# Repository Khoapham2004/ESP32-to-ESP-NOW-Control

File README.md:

The second repository contains the hardware design of the robot. It is mostly based on the 2025 version, with updated sensors, the BTS signal removed from the previous design, and a PCB that primarily uses SMD components for improved compactness and reliability.

The following slide presents the control board developed for the 2026 project.

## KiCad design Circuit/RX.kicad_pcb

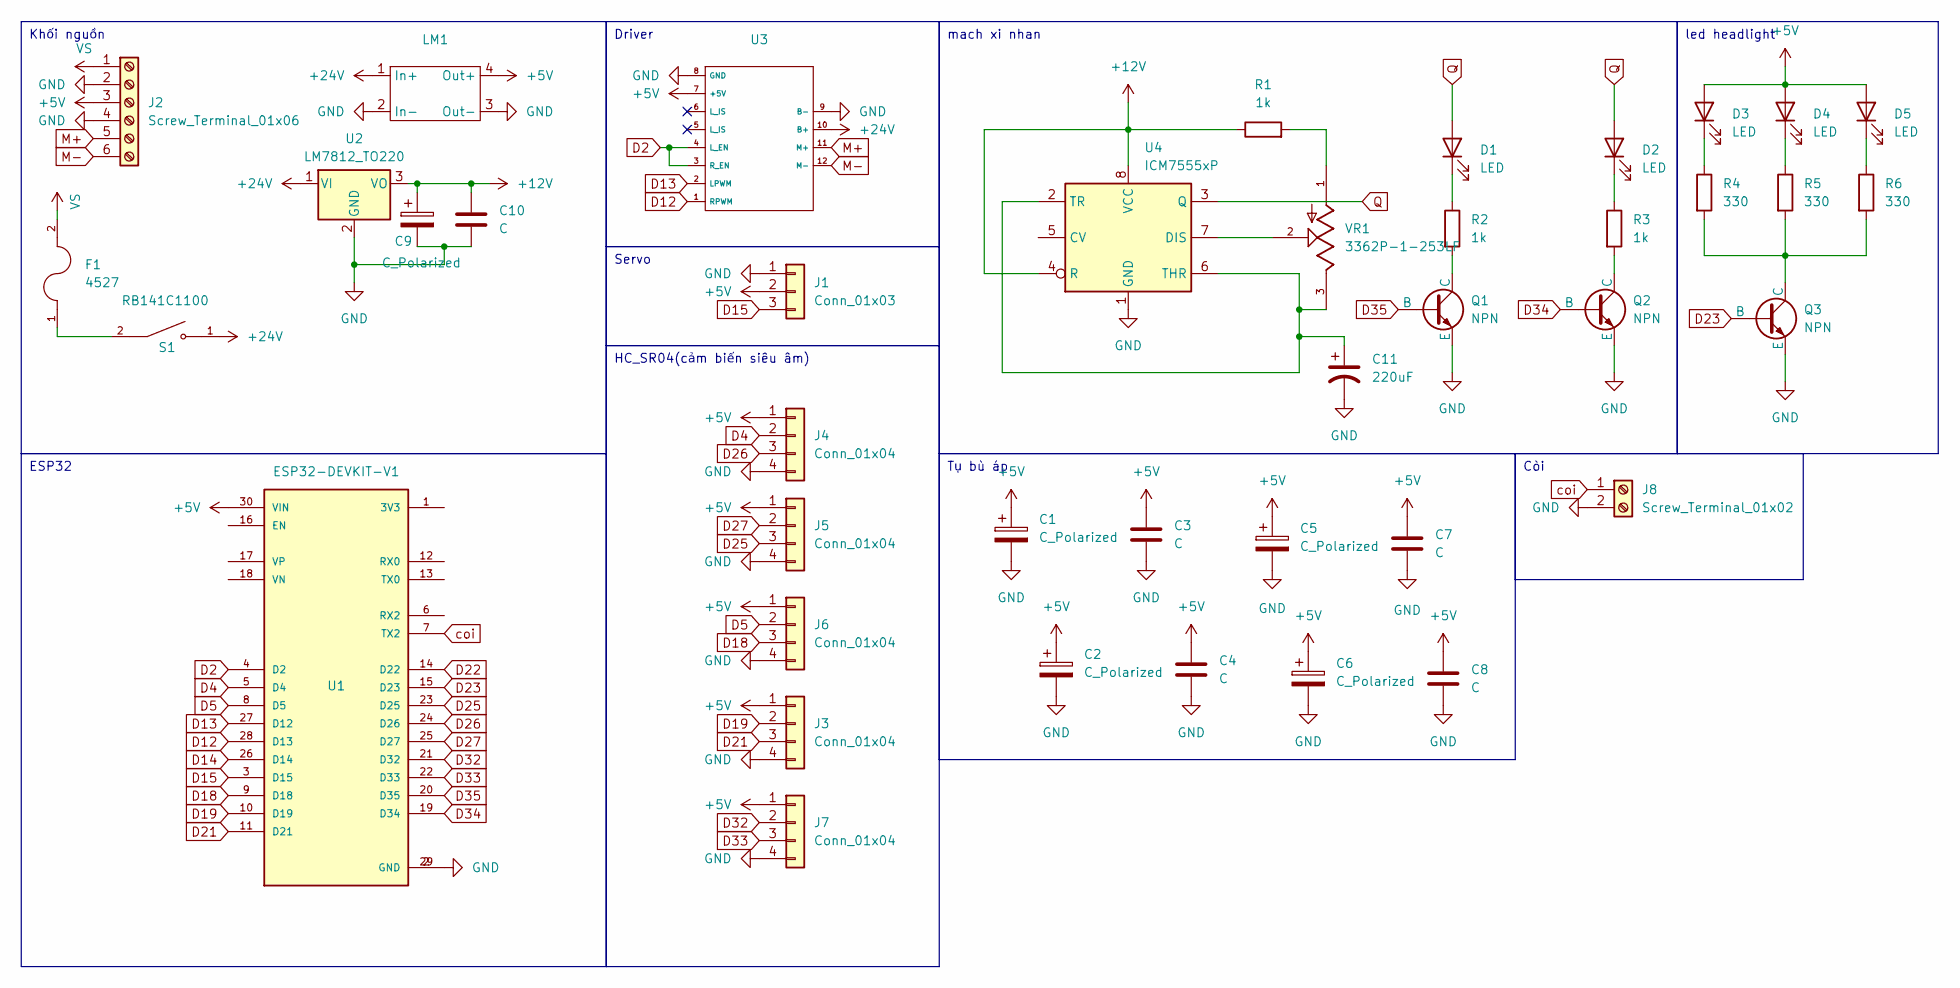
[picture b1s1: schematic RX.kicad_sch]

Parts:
C1, C2, C5, C6, C9: C_Polarized; CP_Radial_D4.0mm_P2.00mm
C3, C4, C7, C8, C10: C; C_Disc_D5.0mm_W2.5mm_P2.50mm
C11: 220uF; CP_Radial_D10.0mm_P3.80mm
D1, D2, D3, D4, D5: LED; LED_D4.0mm
F1: 4527; FUSE_4527; PARTREV B
J1: Conn_01x03; TerminalBlock_Phoenix_MKDS-1,5-3-5.08_1x03_P5.08mm_Horizont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
J2: Screw_Terminal_01x06; TerminalBlock_Phoenix_MKDS-1,5-6-5.08_1x06_P5.08mm_Horizont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
J3, J4, J5, J6, J7: Conn_01x04; PinHeader_1x04_P2.54mm_Vertical
J8: Screw_Terminal_01x02; TerminalBlock_Phoenix_MKDS-1,5-2-5.08_1x02_P5.08mm_Horizont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
LM1: Lm2596
Q1, Q2, Q3: NPN; TO-92L_Inline_Wide
R1, R2, R3: 1k; R_Axial_DIN0204_L3.6mm_D1.6mm_P7.62mm_Horizontal
R4, R5, R6: 330; R_Axial_DIN0204_L3.6mm_D1.6mm_P7.62mm_Horizontal
S1: RB141C1100; SW_POWER; PARTREV C
U1: ESP32-DEVKIT-V1; MODULE_ESP32_DEVKIT_V1; PARTREV N/A
U2: LM7812_TO220; TO-220-3_Vertical
U3: BTS
U4: ICM7555xP; DIP-8_W7.62mm
VR1: 3362P-1-253LF; TRIM_3362P-1-253LF; PARTREV 08/26/10

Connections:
+5V: C1.1, C2.1, C3.1, C4.1, C5.1, C6.1, C7.1, C8.1, D3.2 (A), D4.2 (A), D5.2 (A), J1.2, J2.3, J3.1, J4.1, J5.1, J6.1, J7.1, LM1.4 (Out+), U1.30 (VIN), U3.7 (+5V)
+12V: C9.1, C10.1, R1.1, U2.3 (VO), U4.4 (R), U4.8 (VCC)
+24V: LM1.1 (In+), S1.1, U2.1 (VI), U3.10 (B+)
D2: U1.4 (D2), U3.3 (R_EN), U3.4 (L_EN)
D4: J4.2, U1.5 (D4)
D5: J6.2, U1.8 (D5)
D12: U1.28 (D13), U3.1 (RPWM)
D13: U1.27 (D12), U3.2 (LPWM)
D14: U1.26 (D14)
D15: J1.3, U1.3 (D15)
D18: J6.3, U1.9 (D18)
D19: J3.2, U1.10 (D19)
D21: J3.3, U1.11 (D21)
D22: U1.14 (D22)
D23: Q3.2 (B), U1.15 (D23)
D25: J5.3, U1.23 (D25)
D26: J4.3, U1.24 (D26)
D27: J5.2, U1.25 (D27)
D32: J7.2, U1.21 (D32)
D33: J7.3, U1.22 (D33)
D34: Q2.2 (B), U1.19 (D34)
D35: Q1.2 (B), U1.20 (D35)
GND: C1.2, C2.2, C3.2, C4.2, C5.2, C6.2, C7.2, C8.2, C9.2, C10.2, C11.2, J1.1, J2.2, J2.4, J3.4, J4.4, J5.4, J6.4, J7.4, J8.2, LM1.2 (In-), LM1.3 (Out-), Q1.3 (E), Q2.3 (E), Q3.3 (E), U1.2 (GND), U1.29 (GND), U2.2 (GND), U3.8 (GND), U3.9 (B-), U4.1 (GND)
M+: J2.5, U3.11 (M+)
M-: J2.6, U3.12 (M-)
unnamed: D1.1 (K), R2.1
unnamed: D2.1 (K), R3.1
unnamed: D3.1 (K), R4.1
unnamed: D4.1 (K), R5.1
unnamed: D5.1 (K), R6.1
unnamed: F1.1, S1.2
unnamed: Q1.1 (C), R2.2
unnamed: Q2.1 (C), R3.2
unnamed: Q3.1 (C), R4.2, R5.2, R6.2
unnamed: R1.2, VR1.1
unnamed: U4.7 (DIS), VR1.2
unnamed: C11.1, U4.2 (TR), U4.6 (THR), VR1.3
Q: D1.2 (A), D2.2 (A), U4.3 (Q)
VS: F1.2, J2.1
coi: J8.1, U1.7 (TX2)

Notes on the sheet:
Còi
mach xi nhan
Tụ bù áp
Khối nguồn
HC_SR04(cảm biến siêu âm)
led headlight
Servo
Driver
ESP32

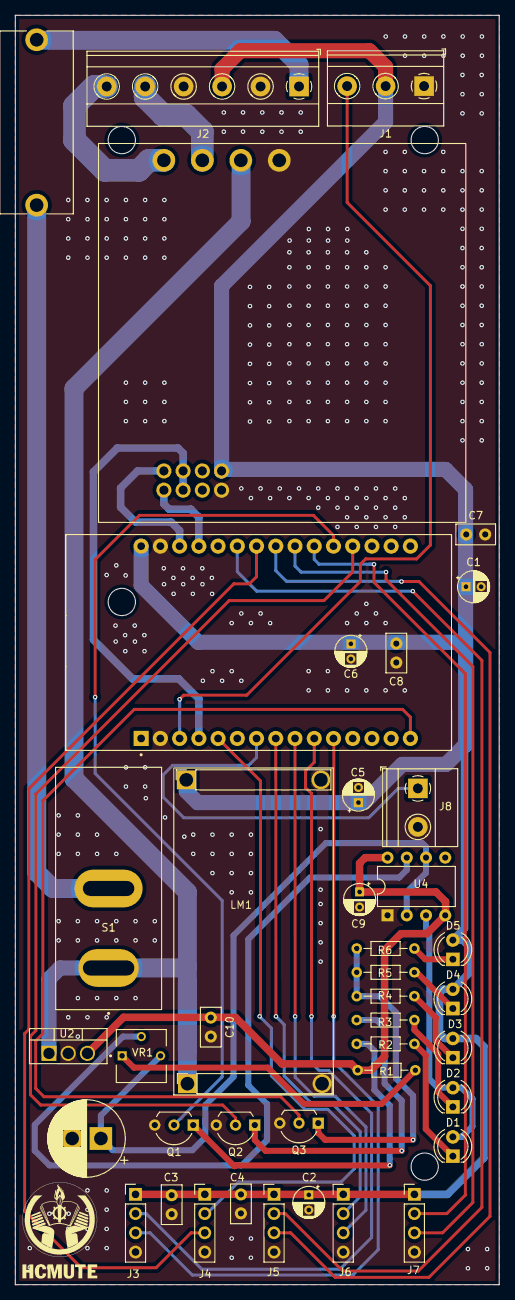
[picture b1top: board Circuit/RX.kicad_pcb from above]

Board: 2 copper layers, 63.9 x 167.6 mm, 41 parts (0 on the bottom side), 38 nets.

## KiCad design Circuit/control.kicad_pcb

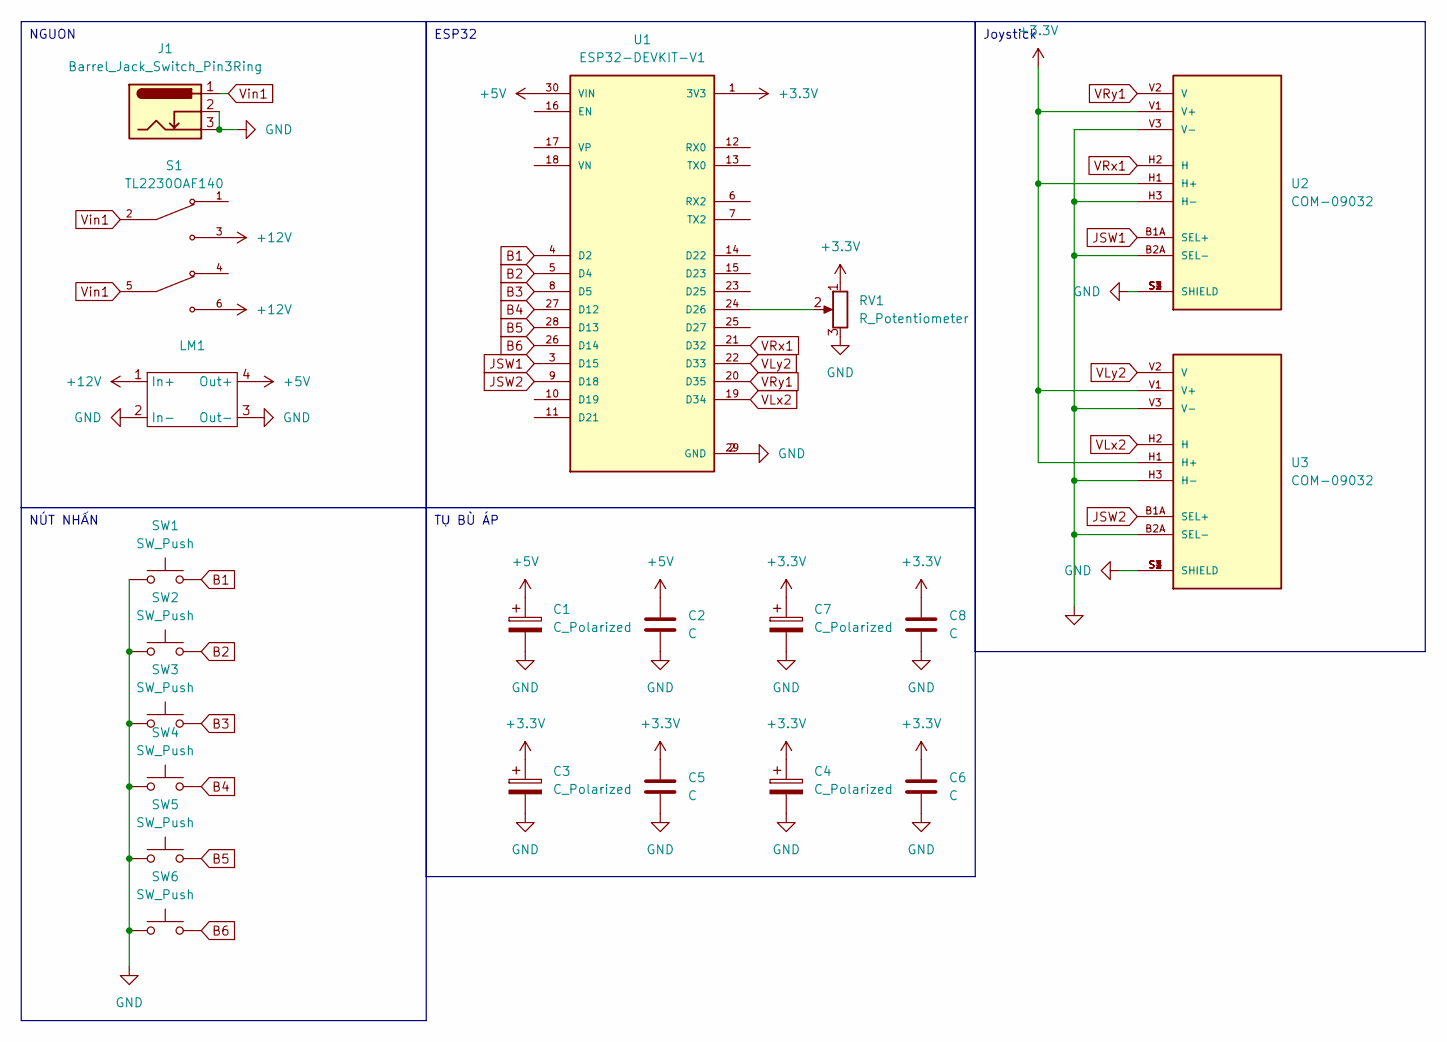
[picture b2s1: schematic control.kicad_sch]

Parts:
C1, C3, C4, C7: C_Polarized; CP_Radial_D4.0mm_P2.00mm
C2, C5, C6, C8: C; C_Disc_D5.0mm_W2.5mm_P2.50mm
J1: Barrel_Jack_Switch_Pin3Ring; BarrelJack_Horizontal
LM1: Lm2596
RV1: R_Potentiometer; Potentiometer_Piher_PC-16_Single_Horizontal
S1: TL2230OAF140; SW_6 pins 8.5×8.5MM; PARTREV E
SW1, SW2, SW3, SW4, SW5, SW6: SW_Push; SW_PUSH_6mm_H9.5mm
U1: ESP32-DEVKIT-V1; MODULE_ESP32_DEVKIT_V1; PARTREV N/A
U2, U3: COM-09032; joystick; PARTREV N/A

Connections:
+3.3V: C3.1, C4.1, C5.1, C6.1, C7.1, C8.1, RV1.1, U1.1 (3V3), U2.H1 (H+), U2.V1 (V+), U3.H1 (H+), U3.V1 (V+)
+5V: C1.1, C2.1, LM1.4 (Out+), U1.30 (VIN)
+12V: LM1.1 (In+), S1.3, S1.6
B1: SW1.2, U1.4 (D2)
B2: SW2.2, U1.5 (D4)
B3: SW3.2, U1.8 (D5)
B4: SW4.2, U1.27 (D12)
B5: SW5.2, U1.28 (D13)
B6: SW6.2, U1.26 (D14)
GND: C1.2, C2.2, C3.2, C4.2, C5.2, C6.2, C7.2, C8.2, J1.2, J1.3, LM1.2 (In-), LM1.3 (Out-), RV1.3, SW1.1, SW2.1, SW3.1, SW4.1, SW5.1, SW6.1, U1.2 (GND), U1.29 (GND), U2.B2A (SEL-), U2.H3 (H-), U2.S1 (SHIELD), U2.S2 (SHIELD), U2.S3 (SHIELD), U2.S4 (SHIELD), U2.V3 (V-), U3.B2A (SEL-), U3.H3 (H-), U3.S1 (SHIELD), U3.S2 (SHIELD), U3.S3 (SHIELD), U3.S4 (SHIELD), U3.V3 (V-)
JSW1: U1.3 (D15), U2.B1A (SEL+)
JSW2: U1.9 (D18), U3.B1A (SEL+)
unnamed: RV1.2, U1.24 (D26)
VLx2: U1.19 (D34), U3.H2 (H)
VLy2: U1.22 (D33), U3.V2 (V)
VRx1: U1.21 (D32), U2.H2 (H)
VRy1: U1.20 (D35), U2.V2 (V)
Vin1: J1.1, S1.2, S1.5

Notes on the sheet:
NÚT NHẤN
ESP32
Joystick
NGUON
TỤ BÙ ÁP

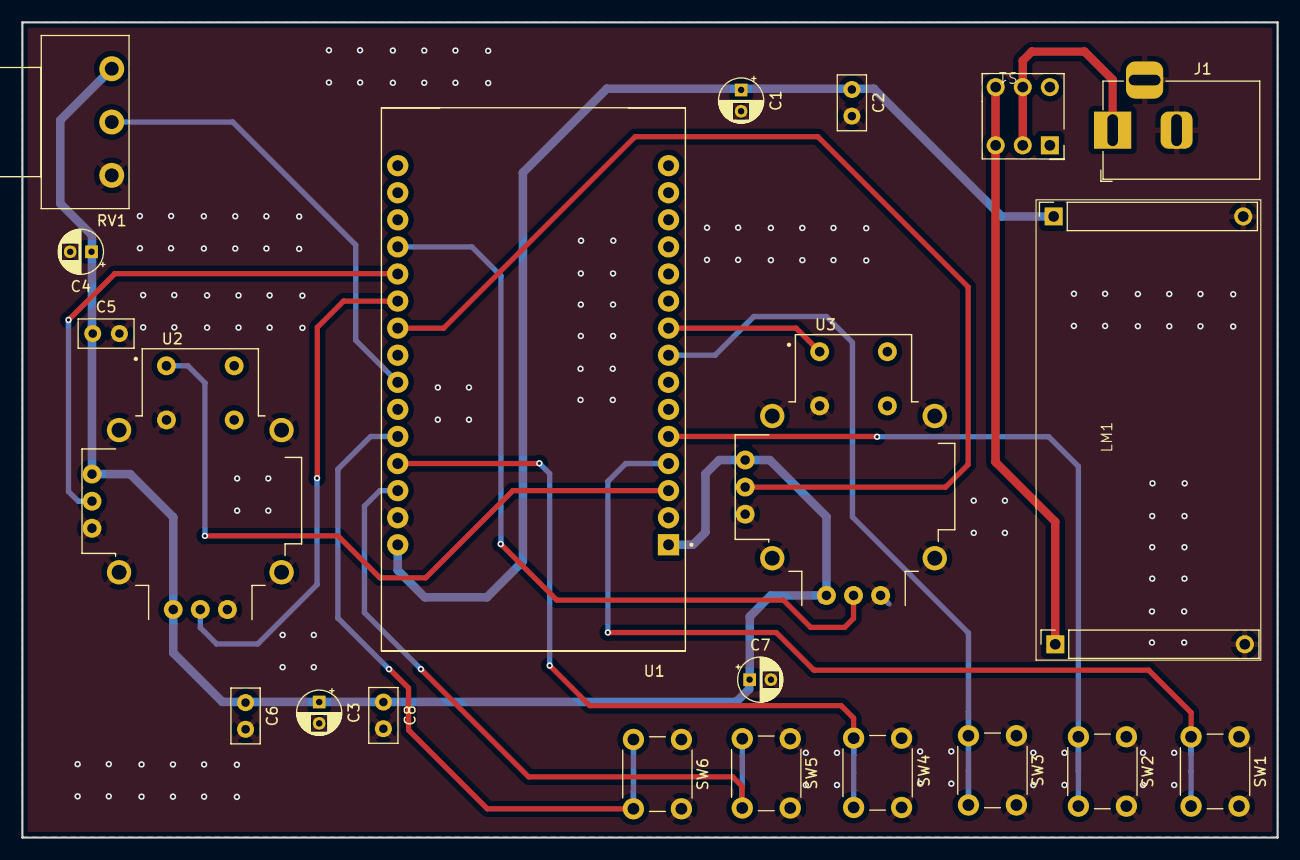
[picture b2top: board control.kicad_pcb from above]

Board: 2 copper layers, 117.7 x 76.5 mm, 21 parts (0 on the bottom side), 18 nets.

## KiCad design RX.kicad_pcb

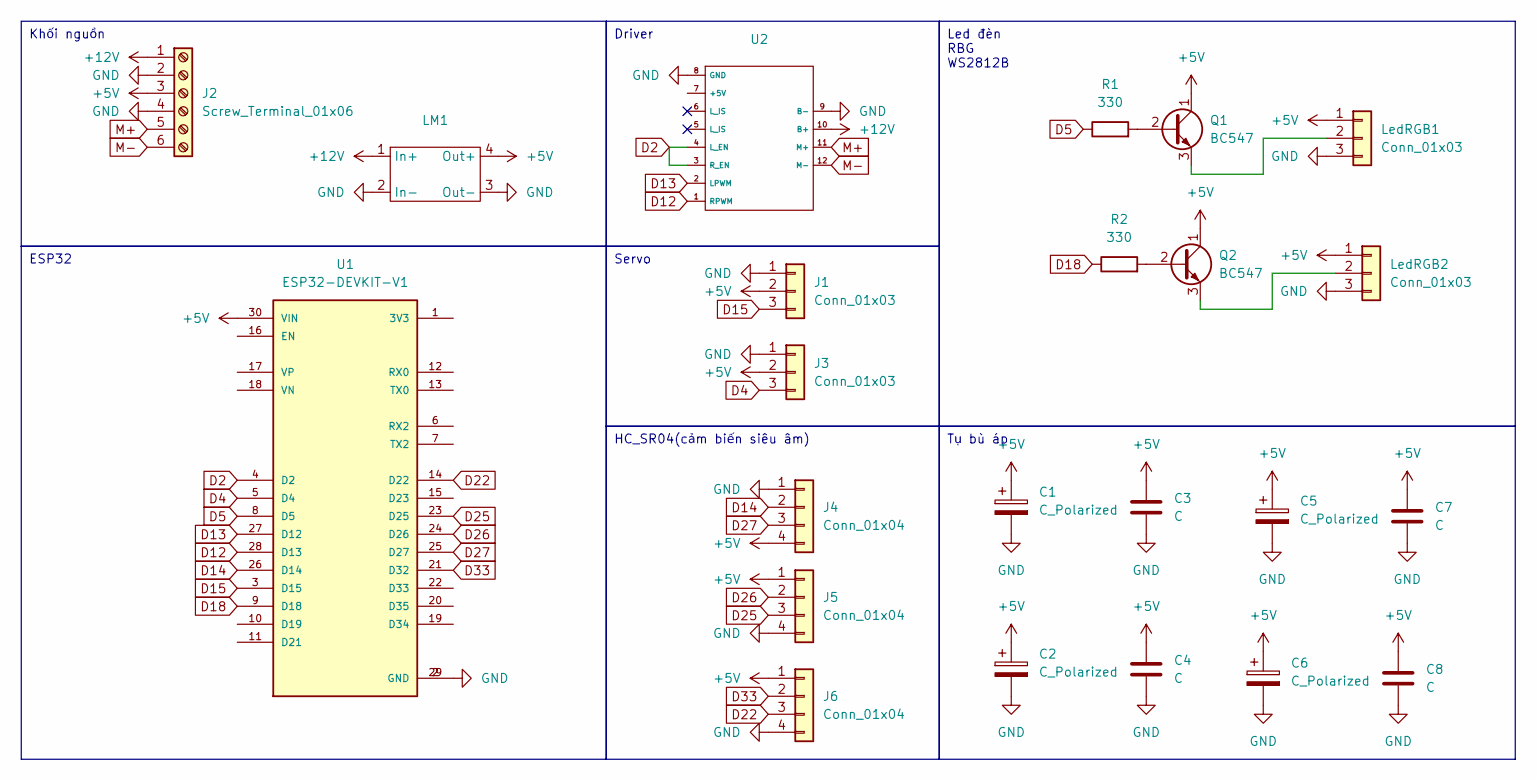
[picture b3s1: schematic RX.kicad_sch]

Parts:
C1, C2, C5, C6: C_Polarized; CP_Radial_D4.0mm_P2.00mm
C3, C4, C7, C8: C; C_Disc_D5.0mm_W2.5mm_P2.50mm
J1, J3: Conn_01x03; TerminalBlock_Phoenix_MKDS-1,5-3-5.08_1x03_P5.08mm_Horizont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
J2: Screw_Terminal_01x06; TerminalBlock_Phoenix_MKDS-1,5-6-5.08_1x06_P5.08mm_Horizont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
J4, J5, J6: Conn_01x04; PinHeader_1x04_P2.54mm_Vertical
LM1: Lm2596
LedRGB1, LedRGB2: Conn_01x03; PinHeader_1x03_P2.54mm_Vertical
Q1, Q2: BC547; TO-92_Inline
R1, R2: 330; R_Axial_DIN0309_L9.0mm_D3.2mm_P12.70mm_Horizontal
U1: ESP32-DEVKIT-V1; MODULE_ESP32_DEVKIT_V1; PARTREV N/A
U2: BTS

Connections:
+5V: C1.1, C2.1, C3.1, C4.1, C5.1, C6.1, C7.1, C8.1, J1.2, J2.3, J3.2, J4.4, J5.1, J6.1, LM1.4 (Out+), LedRGB1.1, LedRGB2.1, Q1.1 (C), Q2.1 (C), U1.30 (VIN)
+12V: J2.1, LM1.1 (In+), U2.10 (B+)
D2: U1.4 (D2), U2.3 (R_EN), U2.4 (L_EN)
D4: J3.3, U1.5 (D4)
D5: R1.1, U1.8 (D5)
D12: U1.28 (D13), U2.1 (RPWM)
D13: U1.27 (D12), U2.2 (LPWM)
D14: J4.2, U1.26 (D14)
D15: J1.3, U1.3 (D15)
D18: R2.1, U1.9 (D18)
D22: J6.3, U1.14 (D22)
D25: J5.3, U1.23 (D25)
D26: J5.2, U1.24 (D26)
D27: J4.3, U1.25 (D27)
D33: J6.2, U1.21 (D32)
GND: C1.2, C2.2, C3.2, C4.2, C5.2, C6.2, C7.2, C8.2, J1.1, J2.2, J2.4, J3.1, J4.1, J5.4, J6.4, LM1.2 (In-), LM1.3 (Out-), LedRGB1.3, LedRGB2.3, U1.2 (GND), U1.29 (GND), U2.8 (GND), U2.9 (B-)
M+: J2.5, U2.11 (M+)
M-: J2.6, U2.12 (M-)
unnamed: LedRGB1.2, Q1.3 (E)
unnamed: LedRGB2.2, Q2.3 (E)
unnamed: Q1.2 (B), R1.2
unnamed: Q2.2 (B), R2.2

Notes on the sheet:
Led đèn RBG WS2812B
Tụ bù áp
Khối nguồn
HC_SR04(cảm biến siêu âm)
Servo
Driver
ESP32

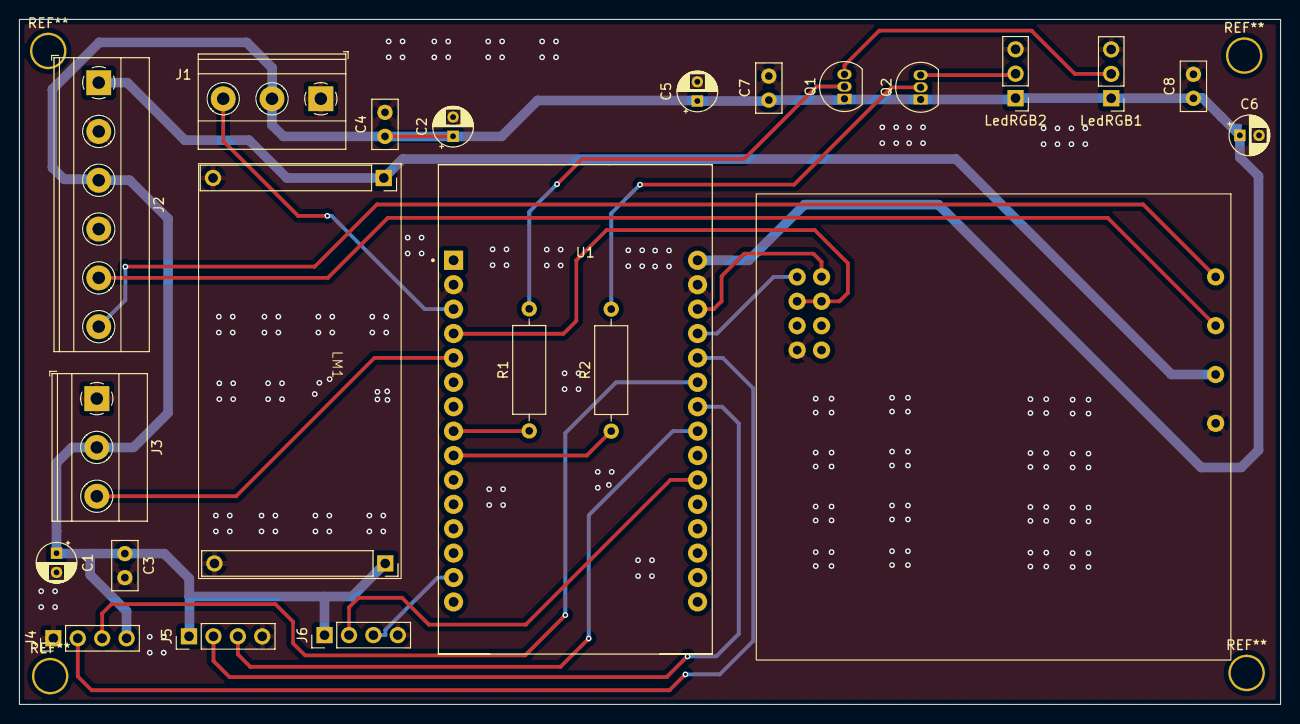
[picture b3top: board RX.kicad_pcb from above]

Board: 2 copper layers, 131.3 x 71.3 mm, 23 parts (0 on the bottom side), 22 nets.

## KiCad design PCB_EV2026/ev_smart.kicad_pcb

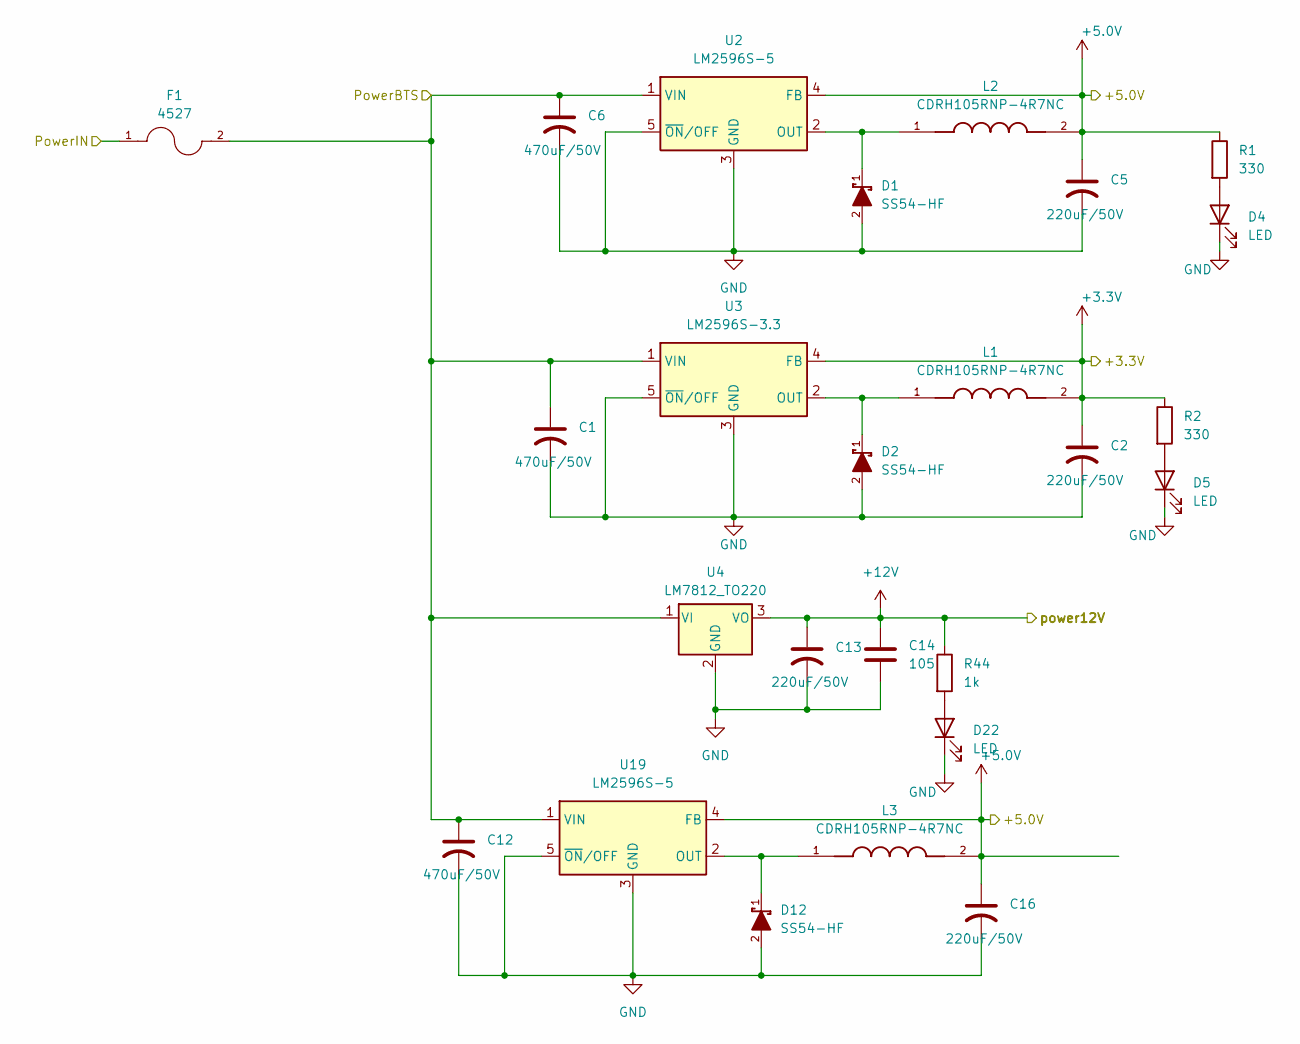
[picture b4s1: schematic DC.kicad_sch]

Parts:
C1, C6, C12: 470uF/50V; CP_Elec_10x10.5
C2, C5, C13, C16: 220uF/50V; CP_Elec_10x10.5
C14: 105; C_0805_2012Metric
D1, D2, D12: SS54-HF; DIOM5025X220N; MOUSER_PART_NUMBER 750-SS54-HF
D4, D5, D22: LED; LED_0805_2012Metric
F1: 4527; FUSE_4527
L1, L2, L3: CDRH105RNP-4R7NC; IND_CDRH105RNP-4R7NC; PARTREV 23-Oct-2017
R1, R2: 330; R_0805_2012Metric_Pad1.20x1.40mm_HandSolder
R44: 1k; R_0805_2012Metric_Pad1.20x1.40mm_HandSolder
U2, U19: LM2596S-5; TO-263-5_TabPin3
U3: LM2596S-3.3; TO-263-5_TabPin3
U4: LM7812_TO220; TO-220-3_Vertical

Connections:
+3.3V: C2.1, L1.2, R2.1, U3.4 (FB); also elsewhere on the board
+5.0V: C5.1, C16.1, L2.2, L3.2, R1.1, U2.4 (FB), U19.4 (FB); also elsewhere on the board
+12V: C13.1, C14.1, R44.1, U4.3 (VO); also elsewhere on the board
/DC-DC/PowerBTS: C1.1, C6.1, C12.1, F1.2, U2.1 (VIN), U3.1 (VIN), U4.1 (VI), U19.1 (VIN); also elsewhere on the board
/DC-DC/PowerIN: F1.1; also elsewhere on the board
GND: C1.2, C2.2, C5.2, C6.2, C12.2, C13.2, C14.2, C16.2, D1.2, D2.2, D4.1 (K), D5.1 (K), D12.2, D22.1 (K), U2.3 (GND), U2.5 (~ON/OFF), U3.3 (GND), U3.5 (~ON/OFF), U4.2 (GND), U19.3 (GND), U19.5 (~ON/OFF); also elsewhere on the board
unnamed: D4.2 (A), R1.2
unnamed: D5.2 (A), R2.2
unnamed: D22.2 (A), R44.2
unnamed: D1.1, L2.1, U2.2 (OUT)
unnamed: D2.1, L1.1, U3.2 (OUT)
unnamed: D12.1, L3.1, U19.2 (OUT)

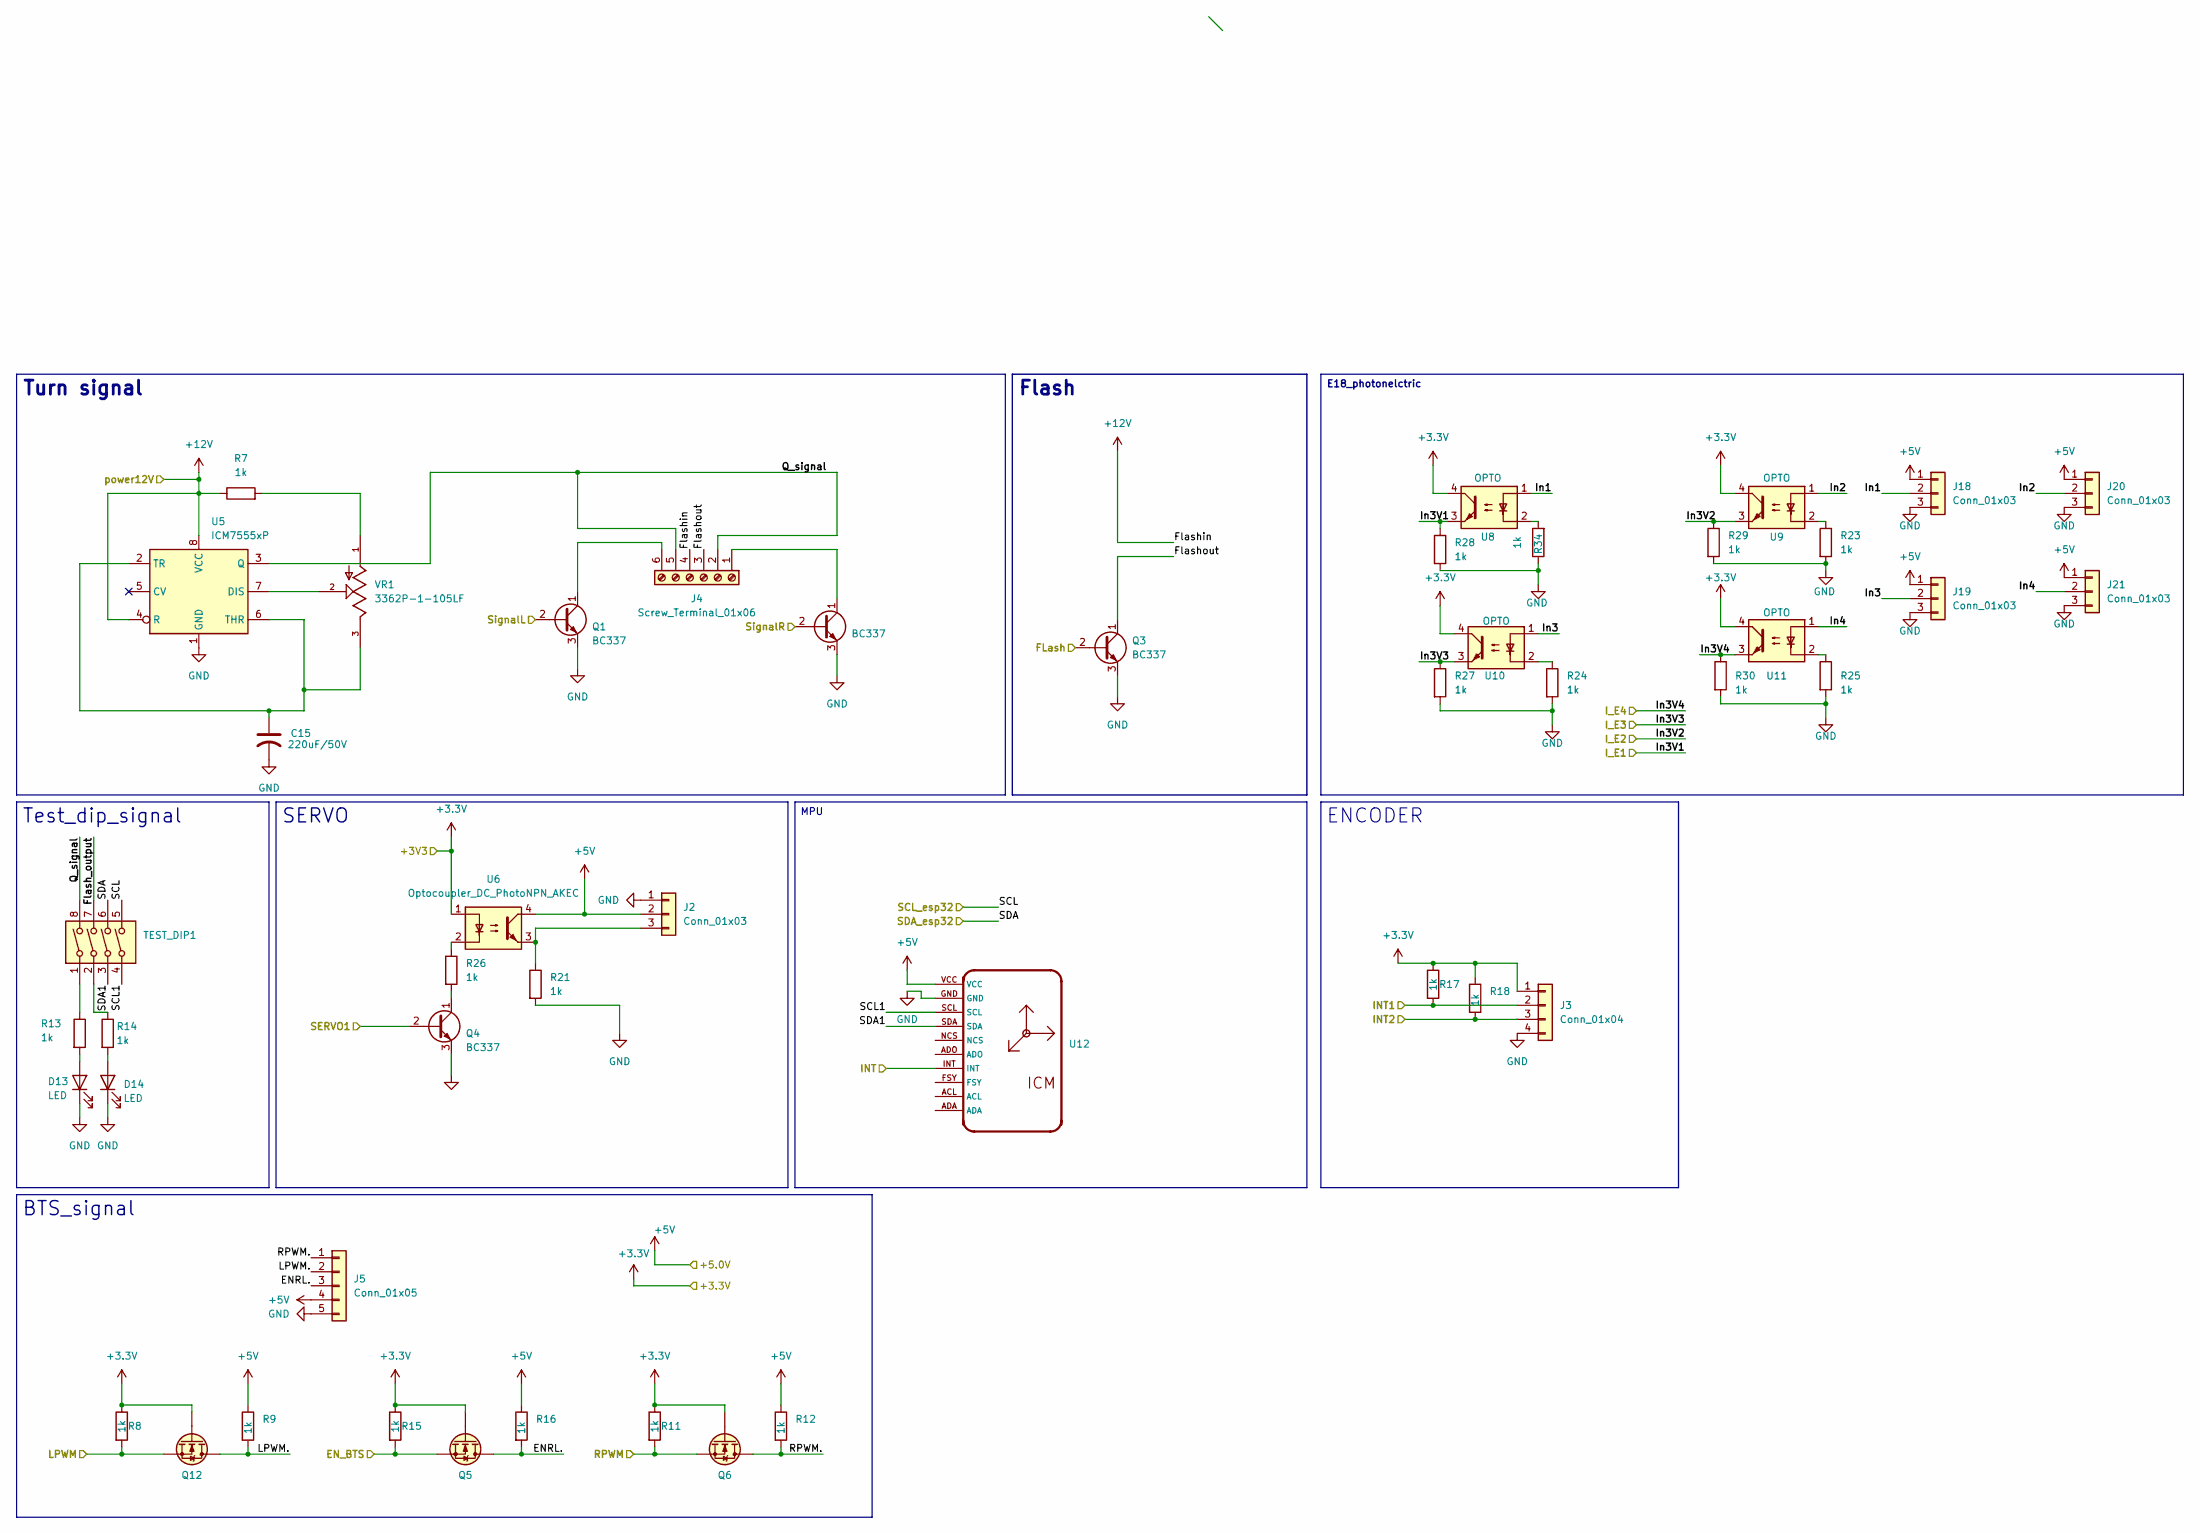
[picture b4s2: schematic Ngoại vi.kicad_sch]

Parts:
C15: 220uF/50V; CP_Elec_10x10.5
D13, D14: LED; LED_0805_2012Metric
J2, J18, J19, J20, J21: Conn_01x03; PinHeader_1x03_P2.54mm_Vertical
J3: Conn_01x04; JST_B4B-XH-A_LF__SN_
J4: Screw_Terminal_01x06; PhoenixContact_MSTBA_2,5_6-G-5,08_1x06_P5.08mm_Horizontal
J5: Conn_01x05; PinHeader_1x05_P2.54mm_Vertical
Q1, Q2, Q3, Q4: BC337; TO-92_Inline
Q5, Q6, Q12: N_Mosfet; SOT-23-3
R7, R8, R9, R11, R12, R13, R14, R15, R16, R17, R18, R21, R23, R24, R25, R26, R27, R28, R29, R30, R34: 1k; R_0805_2012Metric_Pad1.20x1.40mm_HandSolder
TEST_DIP1: SW_DIP_x04; SW_DIP_SPSTx04_Slide_9.78x12.34mm_W7.62mm_P2.54mm
U5: ICM7555xP; DIP-8_W7.62mm
U6: Optocoupler_DC_PhotoNPN_AKEC; OptoIsolation-EL357N-G
U8, U9, U10, U11: OPTO; OptoIsolation-EL357N-G
U12: ICM
VR1: 3362P-1-105LF; TRIM_3362P-1-105LF; PARTREV 08/26/10

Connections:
+3.3V: J3.1, Q5.1 (G), Q6.1 (G), Q12.1 (G), R8.1, R11.1, R15.1, R17.1, R18.1, U6.1, U8.4, U9.4, U10.4, U11.4; also elsewhere on the board
+5.0V: J2.2, J5.4, J18.1, J19.1, J20.1, J21.1, R9.1, R12.1, R16.1, U6.4, U12.VCC; also elsewhere on the board
+12V: J4.4, R7.1, U5.4 (R), U5.8 (VCC); also elsewhere on the board
/Microcontroler/EN_BTS: Q5.2 (S), R15.2; also elsewhere on the board
/Microcontroler/FLash: Q3.2 (B); also elsewhere on the board
/Microcontroler/INT: U12.INT; also elsewhere on the board
/Microcontroler/INT1: J3.2, R17.2; also elsewhere on the board
/Microcontroler/INT2: J3.3, R18.2; also elsewhere on the board
/Microcontroler/LPWM: Q12.2 (S), R8.2; also elsewhere on the board
/Microcontroler/RPWM: Q6.2 (S), R11.2; also elsewhere on the board
/Microcontroler/RX2: Q2.2 (B); also elsewhere on the board
/Microcontroler/SCL_esp32: TEST_DIP1.5; also elsewhere on the board
/Microcontroler/SDA_esp32: TEST_DIP1.6; also elsewhere on the board
/Microcontroler/SERVO1: Q4.2 (B); also elsewhere on the board
/Microcontroler/TX2: Q1.2 (B); also elsewhere on the board
/Ngoại vi/ENRL.: J5.3, Q5.3 (D), R16.2
/Ngoại vi/Flash_output: TEST_DIP1.7
/Ngoại vi/Flashout: J4.3, Q3.1 (C)
/Ngoại vi/In1: J18.2, U8.1
/Ngoại vi/In2: J20.2, U9.1
/Ngoại vi/In3: J19.2, U10.1
/Ngoại vi/In3V1: R28.1, U8.3; also elsewhere on the board
/Ngoại vi/In3V2: R29.1, U9.3; also elsewhere on the board
/Ngoại vi/In3V3: R27.1, U10.3; also elsewhere on the board
/Ngoại vi/In3V4: R30.1, U11.3; also elsewhere on the board
/Ngoại vi/In4: J21.2, U11.1
/Ngoại vi/LPWM.: J5.2, Q12.3 (D), R9.2
/Ngoại vi/Q_signal: J4.2, J4.5, TEST_DIP1.8, U5.3 (Q)
/Ngoại vi/RPWM.: J5.1, Q6.3 (D), R12.2
/Ngoại vi/SCL1: TEST_DIP1.4, U12.SCL
/Ngoại vi/SDA1: TEST_DIP1.3, U12.SDA
GND: C15.2, D13.1 (K), D14.1 (K), J2.1, J3.4, J5.5, J18.3, J19.3, J20.3, J21.3, Q1.3 (E), Q2.3 (E), Q3.3 (E), Q4.3 (E), R21.2, R23.2, R24.2, R25.2, R27.2, R28.2, R29.2, R30.2, R34.1, U5.1 (GND), U12.GND; also elsewhere on the board
unnamed: D13.2 (A), R13.2
unnamed: D14.2 (A), R14.2
unnamed: J2.3, R21.1, U6.3
unnamed: J4.1, Q2.1 (C)
unnamed: J4.6, Q1.1 (C)
unnamed: Q4.1 (C), R26.2
unnamed: R7.2, VR1.1
unnamed: R13.1, TEST_DIP1.1
unnamed: R14.1, TEST_DIP1.2
unnamed: R23.1, U9.2
unnamed: R24.1, U10.2
unnamed: R25.1, U11.2
unnamed: R26.1, U6.2
unnamed: R34.2, U8.2
unnamed: U5.7 (DIS), VR1.2
unnamed: C15.1, U5.2 (TR), U5.6 (THR), VR1.3

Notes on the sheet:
Test_dip_signal
Flash
E18_photonelctric
BTS_signal
Turn signal
SERVO
MPU
ENCODER

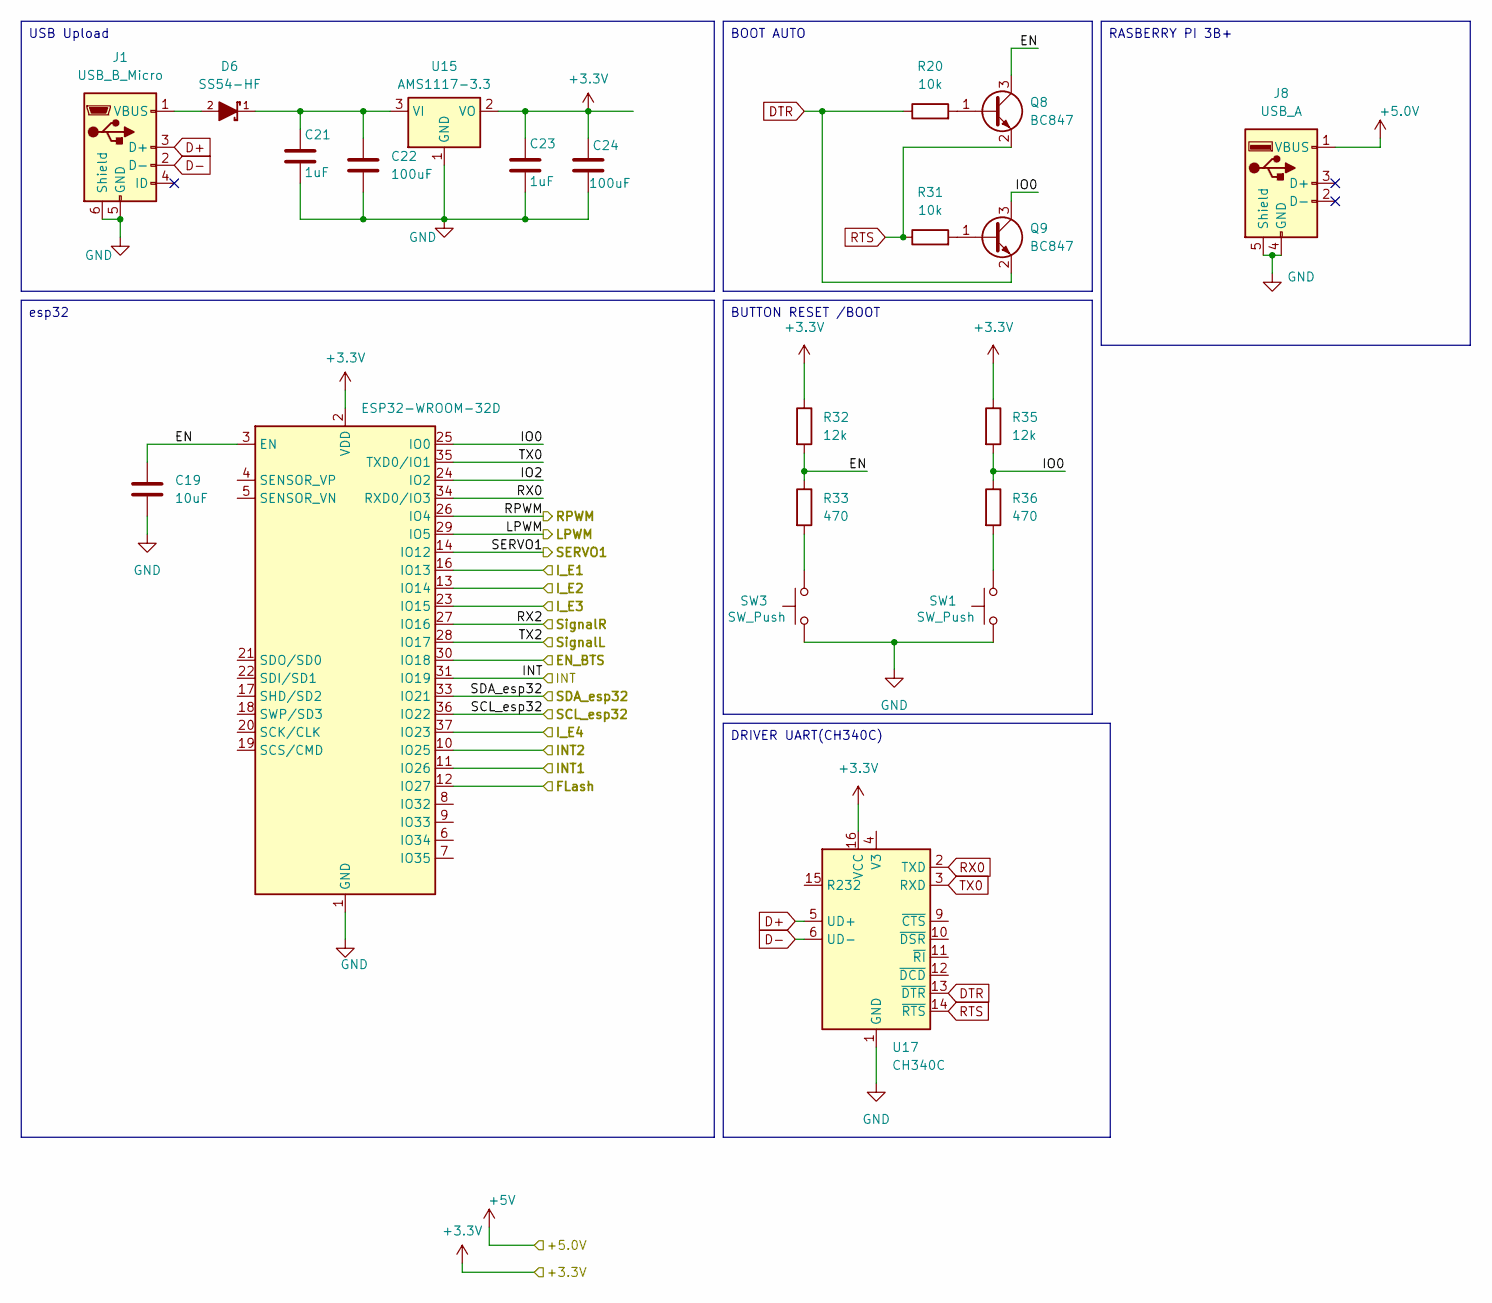
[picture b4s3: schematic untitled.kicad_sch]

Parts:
C19: 10uF; C_0805_2012Metric_Pad1.18x1.45mm_HandSolder
C21, C23: 1uF; C_0805_2012Metric_Pad1.18x1.45mm_HandSolder
C22, C24: 100uF; CP_Elec_6.3x5.4
D6: SS54-HF; DIOM5025X220N; MOUSER_PART_NUMBER 750-SS54-HF
J1: USB_B_Micro; USB_Micro-B_Molex-105017-0001
J8: USB_A; USB_A_Stewart_SS-52100-001_Horizontal
Q8, Q9: BC847; SOT-23
R20, R31: 10k; R_0805_2012Metric_Pad1.20x1.40mm_HandSolder
R32, R35: 12k; R_0805_2012Metric_Pad1.20x1.40mm_HandSolder
R33, R36: 470; R_0805_2012Metric_Pad1.20x1.40mm_HandSolder
SW1, SW3: SW_Push; SW_Push_1P1T_NO_E-Switch_TL3301NxxxxxG
U14: ESP32-WROOM-32D
U15: AMS1117-3.3; SOT-223-3_TabPin2
U17: CH340C; SOIC-16_3.9x9.9mm_P1.27mm

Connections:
+3.3V: C23.1, C24.1, R32.1, R35.1, U14.2 (VDD), U15.2 (VO), U17.16 (VCC); also elsewhere on the board
+5.0V: J8.1 (VBUS); also elsewhere on the board
/Microcontroler/EN: C19.1, Q8.3 (C), R32.2, R33.1, U14.3 (EN)
/Microcontroler/EN_BTS: U14.30 (IO18); also elsewhere on the board
/Microcontroler/FLash: U14.12 (IO27); also elsewhere on the board
/Microcontroler/INT: U14.31 (IO19); also elsewhere on the board
/Microcontroler/INT1: U14.11 (IO26); also elsewhere on the board
/Microcontroler/INT2: U14.10 (IO25); also elsewhere on the board
/Microcontroler/IO0: Q9.3 (C), R35.2, R36.1, U14.25 (IO0)
/Microcontroler/IO2: U14.24 (IO2)
/Microcontroler/LPWM: U14.29 (IO5); also elsewhere on the board
/Microcontroler/RPWM: U14.26 (IO4); also elsewhere on the board
/Microcontroler/RX2: U14.27 (IO16); also elsewhere on the board
/Microcontroler/SCL_esp32: U14.36 (IO22); also elsewhere on the board
/Microcontroler/SDA_esp32: U14.33 (IO21); also elsewhere on the board
/Microcontroler/SERVO1: U14.14 (IO12); also elsewhere on the board
/Microcontroler/TX2: U14.28 (IO17); also elsewhere on the board
/Ngoại vi/In3V1: U14.16 (IO13); also elsewhere on the board
/Ngoại vi/In3V2: U14.13 (IO14); also elsewhere on the board
/Ngoại vi/In3V3: U14.23 (IO15); also elsewhere on the board
/Ngoại vi/In3V4: U14.37 (IO23); also elsewhere on the board
D+: J1.3 (D+), U17.5 (UD+)
D-: J1.2 (D-), U17.6 (UD-)
DTR: Q9.2 (E), R20.1, U17.13 (~DTR)
GND: C19.2, C21.2, C22.2, C23.2, C24.2, J1.5 (GND), J1.6 (Shield), J8.4 (GND), J8.5 (Shield), SW1.1, SW3.1, U14.1 (GND), U14.15 (GND), U14.38 (GND), U14.39 (GND), U15.1 (GND), U17.1 (GND); also elsewhere on the board
unnamed: D6.2, J1.1 (VBUS)
unnamed: Q8.1 (B), R20.2
unnamed: Q9.1 (B), R31.2
unnamed: R33.2, SW3.2
unnamed: R36.2, SW1.2
unnamed: C21.1, C22.1, D6.1, U15.3 (VI)
RTS: Q8.2 (E), R31.1, U17.14 (~RTS)
RX0: U14.34 (RXD0/IO3), U17.2 (TXD)
TX0: U14.35 (TXD0/IO1), U17.3 (RXD)

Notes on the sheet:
RASBERRY PI 3B+
DRIVER UART(CH340C)
BOOT AUTO
BUTTON RESET /BOOT
USB Upload
esp32
